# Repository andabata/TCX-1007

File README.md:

The story so far.. 
https://mastodon.social/deck/@andabata/113323217821912792

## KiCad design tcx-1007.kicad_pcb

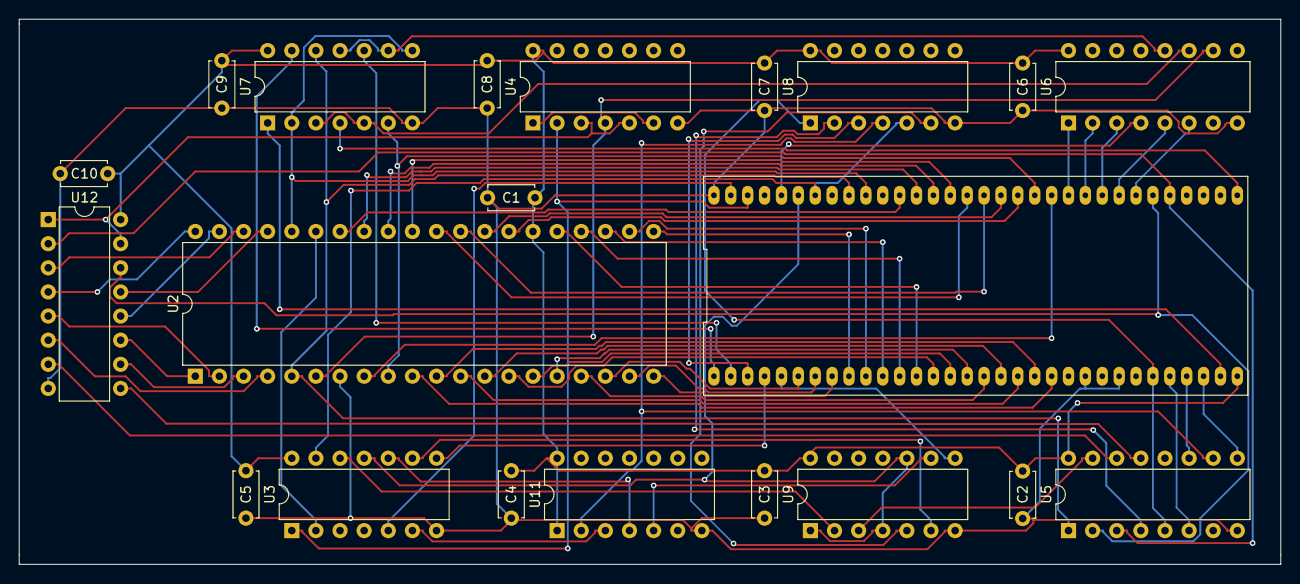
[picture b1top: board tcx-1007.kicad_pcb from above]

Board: 2 copper layers, 132.8 x 57.4 mm, 21 parts (0 on the bottom side), 78 nets.

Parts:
C1, C2, C3, C4, C5, C6, C7, C8, C9, C10: 0.1uF; C_Disc_D4.7mm_W2.5mm_P5.00mm
U1: TCX-1007; DIP-64_750_ELL
U2: 8255; DIP-40_W15.24mm
U3: 74LS04; DIP-14_W7.62mm
U4: 74LS00; DIP-14_W7.62mm
U5: 74LS139; DIP-16_W7.62mm
U6: 74LS138; DIP-16_W7.62mm
U7: 74LS02; DIP-14_W7.62mm
U8: 74LS08; DIP-14_W7.62mm
U9: 74LS32; DIP-14_W7.62mm
U11: 74LS74; DIP-14_W7.62mm
U12: 74LS153; DIP-16_W7.62mm

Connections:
A0: U1.45 (A0), U2.9 (A0), U7.6
A1: U1.44 (A1), U2.8 (A1)
A3: U1.43 (A3), U6.1 (A0)
A4: U1.42 (A4), U6.2 (A1)
A5: U1.41 (A5), U6.3 (A2)
A6: U1.40 (A6), U6.5 (E2)
A7: U1.39 (A7), U6.6 (E3)
A14: U1.38 (A14), U5.2 (A0), U12.14 (S0)
A15: U1.37 (A15), U5.3 (A1), U12.2 (S1)
BC1: U1.33 (PSG-BC1), U7.4
BDIR: U1.31 (PSG-BDIR), U7.1
CLOCK: U1.63 (CLOCK), U3.5
CS_PPI: U2.6 (~CS), U4.4, U6.10 (O5)
CS_PSG: U6.11 (O4), U7.3, U7.5
CS_VDP: U6.12 (O3), U7.9, U7.11
D0: U1.53 (D0), U2.34 (D0)
D1: U1.52 (D1), U2.33 (D1)
D2: U1.51 (D2), U2.32 (D2)
D3: U1.50 (D3), U2.31 (D3)
D4: U1.49 (D4), U2.30 (D4)
D5: U1.48 (D5), U2.29 (D5)
D6: U1.47 (D6), U2.28 (D6)
D7: U1.46 (D7), U2.27 (D7)
GND: C1.2, C2.2, C3.2, C4.2, C5.2, C6.2, C7.2, C8.2, C9.2, C10.2, U1.23 (GND), U1.25 (GND), U1.64 (GND), U2.7 (GND), U3.7 (GND), U4.7 (GND), U5.8 (GND), U6.8 (GND), U7.7 (GND), U8.7 (GND), U9.7 (GND), U11.7 (GND), U12.8 (GND)
MUX: U1.4 (MUX), U3.8
unnamed: U3.9, U9.6
unnamed: U3.12, U9.2
unnamed: U4.1, U4.6
unnamed: U5.4 (O0), U8.2
unnamed: U5.15 (E), U9.3
unnamed: U8.6, U9.5
unnamed: U3.6, U11.3 (C)
unnamed: U9.9, U11.5 (Q)
unnamed: U3.10, U11.4 (~S)
unnamed: U4.3, U4.5, U12.1 (Ea), U12.15 (Eb)
unnamed: U2.4 (PA0), U12.6 (I0a)
unnamed: U2.3 (PA1), U12.10 (I0b)
unnamed: U2.2 (PA2), U12.5 (I1a)
unnamed: U2.1 (PA3), U12.11 (I1b)
unnamed: U2.40 (PA4), U12.4 (I2a)
unnamed: U2.39 (PA5), U12.12 (I2b)
unnamed: U2.38 (PA6), U12.3 (I3a)
unnamed: U2.37 (PA7), U12.13 (I3b)
unnamed: U5.14 (A0), U12.7 (Za)
unnamed: U5.13 (A1), U12.9 (Zb)
PB0: U1.6 (PPI-PB0), U2.18 (PB0)
PB1: U1.7 (PPI-PB1), U2.19 (PB1)
PB2: U1.8 (PPI-PB2), U2.20 (PB2)
PB3: U1.9 (PPI-PB3), U2.21 (PB3)
PB4: U1.10 (PPI-PB4), U2.22 (PB4)
PB5: U1.11 (PPI-PB5), U2.23 (PB5)
PB6: U1.12 (PPI-PB6), U2.24 (PB6)
PB7: U1.13 (PPI-PB7), U2.25 (PB7)
PC0: U1.14 (PPI-PC0), U2.14 (PC0)
PC1: U1.15 (PPI-PC1), U2.15 (PC1)
PC2: U1.16 (PPI-PC2), U2.16 (PC2)
PC3: U1.17 (PPI-PC3), U2.17 (PC3)
PC4: U1.18 (PPI-PC4), U2.13 (PC4)
PC5: U1.19 (PPI-PC5), U2.12 (PC5)
PC6: U1.20 (PPI-PC6), U2.11 (PC6)
PC7: U1.21 (PPI-PC7), U2.10 (PC7)
RESET: U2.35 (RESET), U3.2
VCC: C1.1, C2.1, C3.1, C4.1, C5.1, C6.1, C7.1, C8.1, C9.1, C10.1, U1.32 (VCC), U2.26 (VCC), U3.14 (VCC), U4.14 (VCC), U5.16 (VCC), U6.16 (VCC), U7.14 (VCC), U8.14 (VCC), U9.14 (VCC), U11.1 (~R), U11.14 (VCC), U12.16 (VCC)
~CAS: U1.5 (~CAS), U9.8
~CS1: U1.27 (~CS1), U5.5 (O1), U8.1
~CS01: U1.3 (~CS01), U8.3
~CS2: U1.28 (~CS2), U5.6 (O2)
~CSR: U1.1 (~VDP-CSR), U7.13
~CSW: U1.2 (~VDP-CSW), U7.10
~IOREQ: U1.60 (~Z80-IOREQ), U6.4 (E1)
~MREQ: U1.59 (~Z80-MREQ), U3.11, U9.1, U9.4, U9.10
~RD: U1.56 (~Z80-RD), U2.5 (~RD), U5.1 (E), U7.12
~REFSH: U1.58 (~Z80-REFSH), U3.13, U8.5
~RESET: U1.62 (~RESET), U3.1, U4.2
~SLTSL1: U1.29 (~SLTLS1), U5.11 (O1)
~SLTSL2: U5.10 (O2), U8.4, U11.2 (D)
~SLTSL3: U1.30 (~SLTLS3), U5.9 (O3)
~WR: U1.55 (~Z80-WR), U2.36 (~WR), U7.2, U7.8
